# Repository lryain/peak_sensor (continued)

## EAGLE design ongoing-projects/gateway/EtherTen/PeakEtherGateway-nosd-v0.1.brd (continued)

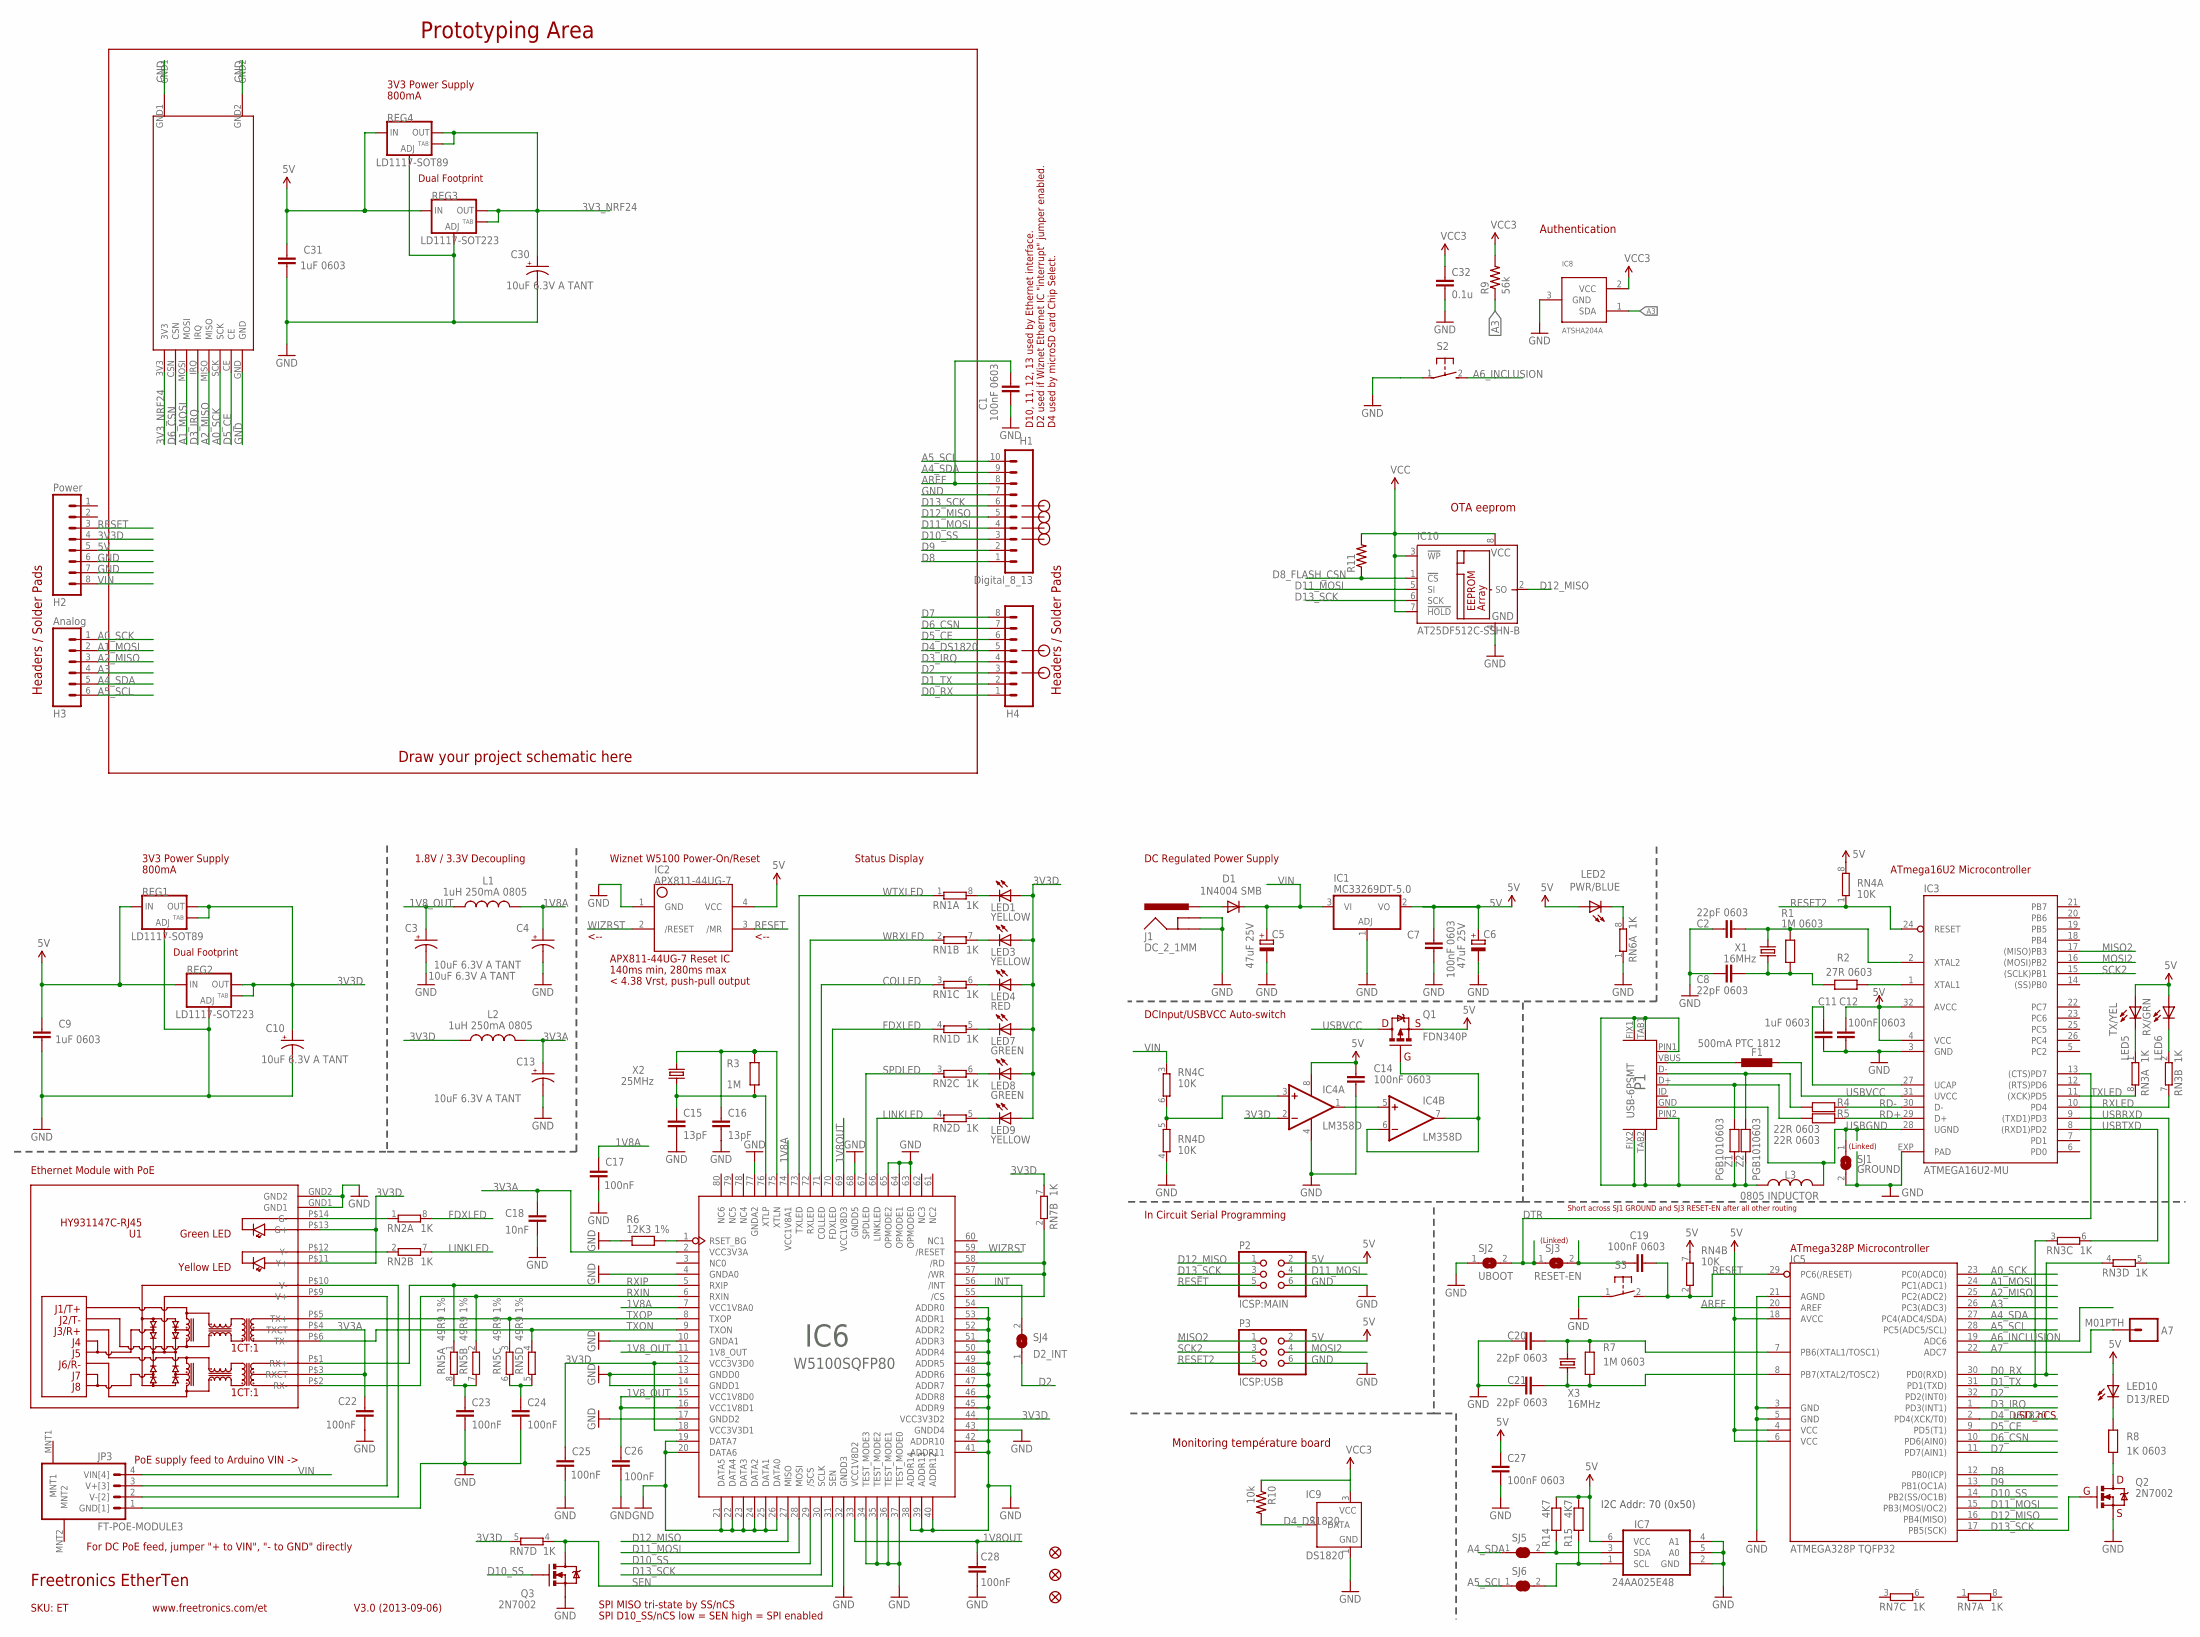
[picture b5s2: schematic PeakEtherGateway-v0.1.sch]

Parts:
A7: M01PTH; 1X01
C1, C7, C12, C14, C19, C27: 100nF 0603; 0603
C2, C8, C20, C21: 22pF 0603; 0603
C3, C4, C10, C13, C30: 10uF 6.3V A TANT; EIA3216
C5, C6: 47uF 25V; PANASONIC_D
C9, C11, C31: 1uF 0603; 0603
C15, C16: 13pF; 0603
C17, C22, C23, C24, C25, C26, C28: 100nF; 0603
C18: 10nF; 0603
C32: 0.1u; 0603-CAP
D1: 1N4004 SMB; SMB-DIODE
F1: 500mA PTC 1812; L1812
FID1, FID2, FID3: FIDUCIAL1X2.5; FIDUCIAL-1X2.5
H1: Digital_8_13; 1X10
H2: Power; 1X08
H3: Analog; 1X06
H4: Digital_0_7; 1X08
IC1: MC33269DT-5.0; DPACK
IC2: APX811-44UG-7; SOT143-R
IC3: ATMEGA16U2-MU; ATMEL_QFN32
IC4: LM358D; SO08
IC5: ATMEGA328P TQFP32; TQFP32-08
IC6: W5100SQFP80; SQFP80
IC7: 24AA025E48; SOT23-6
IC8: ATSHA204A; SOT23
IC9: DS1820; TO92-
IC10: AT25DF512C-SSHN-B; SO-08
J1: DC_2_1MM; POWER_JACK_PTH
JP3: FT-POE-MODULE3; FT-POE-MODULE-NOLABEL
L1, L2: 1uH 250mA 0805; L2012C
L3: 0805 INDUCTOR; 0805-LARGE
LED1, LED3, LED9: YELLOW; LED-0603
LED2: PWR/BLUE; LED-0603
LED4: RED; LED-0603
LED5: TX/YEL; LED-0603
LED6: RX/GRN; LED-0603
LED7, LED8: GREEN; LED-0603
LED10: D13/RED; LED-0603
P1: USB-6PSMT; USB-MICROB-MB05PMXX
P2: ICSP:MAIN; 2X03
P3: ICSP:USB; 2X03
Q1: FDN340P; SOT23
Q2, Q3: 2N7002; SOT23-3
R1, R7: 1M 0603; 0603
R2: 27R 0603; 0603
R3: 1M; 0603
R4, R5: 22R 0603; 0603
R6: 12K3 1%; 0603
R8: 1K 0603; 0603
R9: 56k; 0603-RES
R10: 10k; 0603-RES
R11: RESISTOR0603-RES; 0603-RES
R14, R15: 4K7; 0603
REG1, REG4: LD1117-SOT89; SOT89
REG2, REG3: LD1117-SOT223; SOT223
RN1, RN2, RN3, RN6, RN7: 1K; CAY16
RN4: 10K; CAY16
RN5: 49R9 1%; CAY16
S2, S3: 31-XX; B3F-31XX
SJ1: GROUND; SJ
SJ2: UBOOT; SJ
SJ3: RESET-EN; SJ
SJ4: D2_INT; SJ
SJ5, SJ6: SJCN; SJC
U1: HY931147C-RJ45; HY931147C
U$17: NRF2401; NRF2401_PA_OUTLINE
X1, X3: 16MHz; HC49U-V
X2: 25MHz; HC49U-V
Z1, Z2: PGB1010603; 0603

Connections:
1V8A: C4.A (+), C17.1, IC6.7 (VCC1V8A0), IC6.74 (VCC1V8A1), L1.2
1V8OUT: C28.1, IC6.33 (VCC1V8D2), IC6.69 (VCC1V8D3)
1V8_OUT: C3.A (+), C26.1, IC6.11 (1V8_OUT), IC6.15 (VCC1V8D0), IC6.16 (VCC1V8D1), L1.1
3V3A: C13.A (+), C18.1, C22.1, IC6.2 (VCC3V3A), L2.2, U1.P$3 (RXCT), U1.P$4 (TXCT)
3V3D: C10.A (+), C25.1, H2.4, IC4.2 (-IN), IC6.12 (VCC3V3D0), IC6.18 (VCC3V3D1), IC6.44 (VCC3V3D2), L2.1, LED1.A, LED3.A, LED4.A, LED7.A, LED8.A, LED9.A, REG1.2 (OUT), REG1.4 (OUT), REG2.2 (OUT), REG2.4 (OUT), RN7.5 (2), RN7.7 (2), U1.P$11 (Y+), U1.P$13 (G+)
3V3_NRF24: C30.A (+), C32.1, IC8.2 (VCC), IC9.3 (VCC), IC10.3 (!WP), IC10.7 (!HOLD), IC10.8 (VCC), R9.2, R10.1, R11.2, REG3.2 (OUT), REG3.4 (OUT), REG4.2 (OUT), REG4.4 (OUT), U$17.3V3
5V: C6.+, C7.1, C9.1, C12.1, C14.1, C27.1, C31.1, H2.5, IC1.2 (VO), IC2.4 (VCC), IC3.4 (VCC), IC3.32 (AVCC), IC4.8 (V+), IC5.4 (VCC), IC5.6 (VCC), IC5.18 (AVCC), IC7.6 (VCC), LED2.A, LED5.A, LED6.A, LED10.A, P2.2, P3.2, Q1.2 (S), R14.1, R15.1, REG1.3 (IN), REG2.3 (IN), REG3.3 (IN), REG4.3 (IN), RN4.7 (2), RN4.8 (2)
A0_SCK: H3.1, IC5.23 (PC0(ADC0)), U$17.SCK
A1_MOSI: H3.2, IC5.24 (PC1(ADC1)), U$17.MOSI
A2_MISO: H3.3, IC5.25 (PC2(ADC2)), U$17.MISO
A3: H3.4, IC5.26 (PC3(ADC3)), IC8.1 (SDA), R9.1
A4_SDA: H1.9, H3.5, IC5.27 (PC4(ADC4/SDA)), SJ5.1
A5_SCL: H1.10, H3.6, IC5.28 (PC5(ADC5/SCL)), SJ6.1
A6_INCLUSION: IC5.19 (ADC6), S2.2 (S)
A7: A7.1, IC5.22 (ADC7)
AREF: C1.1, H1.8, IC5.20 (AREF)
COLLED: IC6.71 (COLLED), RN1.3 (1)
D0_RX: H4.1, IC5.30 (PD0(RXD)), RN3.4 (1)
D1_TX: H4.2, IC5.31 (PD1(TXD)), RN3.3 (1)
D2: H4.3, IC5.32 (PD2(INT0)), SJ4.1
D3_IRQ: H4.4, IC5.1 (PD3(INT1)), U$17.IRQ
D4_DS1820: H4.5, IC5.2 (PD4(XCK/T0)), IC9.2 (DATA), R10.2
D5_CE: H4.6, IC5.9 (PD5(T1)), U$17.CE
D6_CSN: H4.7, IC5.10 (PD6(AIN0)), U$17.CSN
D7: H4.8, IC5.11 (PD7(AIN1))
D8: H1.1, IC5.12 (PB0(ICP))
D8_FLASH_CSN: IC10.1 (!CS), R11.1
D9: H1.2, IC5.13 (PB1(OC1A))
D10_SS: H1.3, IC5.14 (PB2(SS/OC1B)), IC6.29 (/SCS), Q3.1 (G)
D11_MOSI: H1.4, IC5.15 (PB3(MOSI/OC2)), IC6.28 (MOSI), IC10.5 (SI), P2.4
D12_MISO: H1.5, IC5.16 (PB4(MISO)), IC6.27 (MISO), IC10.2 (SO), P2.1
D13_SCK: H1.6, IC5.17 (PB5(SCK)), IC6.30 (SCLK), IC10.6 (SCK), P2.3, Q2.1 (G)
DTR: IC3.13 ((CTS)PD7), SJ2.2, SJ3.1
FDXLED: IC6.70 (FDXLED), RN1.4 (1), RN2.8 (2)
GND: C1.2, C2.1, C3.C (-), C4.C (-), C5.-, C6.-, C7.2, C8.1, C9.2, C10.C (-), C11.2, C12.2, C13.C (-), C14.2, C15.2, C16.2, C17.2, C18.2, C20.1, C21.1, C22.2, C23.2, C24.2, C25.2, C26.2, C27.2, C28.2, C30.C (-), C31.2, C32.2, H1.7, H2.6, H2.7, IC1.1 (ADJ), IC2.1 (GND), IC3.3 (GND), IC3.EXP (PAD), IC4.4 (V-), IC5.3 (GND), IC5.5 (GND), IC5.21 (AGND), IC6.4 (GNDA0), IC6.10 (GNDA1), IC6.13 (GNDD0), IC6.14 (GNDD1), IC6.17 (GNDD2), IC6.19 (DATA7), IC6.20 (DATA6), IC6.21 (DATA5), IC6.22 (DATA4), IC6.23 (DATA3), IC6.24 (DATA2), IC6.25 (DATA1), IC6.26 (DATA0), IC6.32 (GNDD3), IC6.34 (TEST_MODE3), IC6.35 (TEST_MODE2), IC6.36 (TEST_MODE1), IC6.37 (TEST_MODE0), IC6.38 (ADDR14), IC6.39 (ADDR13), IC6.40 (ADDR12), IC6.41 (ADDR11), IC6.42 (ADDR10), IC6.43 (GNDD4), IC6.45 (ADDR9), IC6.46 (ADDR8), IC6.47 (ADDR7), IC6.48 (ADDR6), IC6.49 (ADDR5), IC6.50 (ADDR4), IC6.51 (ADDR3), IC6.52 (ADDR2), IC6.53 (ADDR1), IC6.54 (ADDR0), IC6.63 (OPMODE0), IC6.64 (OPMODE1), IC6.65 (OPMODE2), IC6.68 (GNDD5), IC6.77 (GNDA2), IC7.2 (GND), IC7.4 (A1), IC7.5 (A0), IC8.3 (GND), IC9.1 (GND), IC10.4 (GND), J1.GND, J1.GNDBREAK, JP3.1 (GND[1]), P2.6, P3.6, Q2.2 (S), Q3.2 (S), R6.1, REG1.1 (ADJ), REG2.1 (ADJ), REG3.1 (ADJ), REG4.1 (ADJ), RN4.4 (1), RN6.1, S2.1, S3.1, SJ1.2, SJ2.1, U1.GND1, U1.GND2, U$17.GND
INT: IC6.56 (/INT), SJ4.2
LINKLED: IC6.66 (LINKLED), RN2.4 (1), RN2.7 (2)
MISO2: IC3.17 ((MISO)PB3), P3.1
MOSI2: IC3.16 ((MOSI)PB2), P3.4
unnamed: C24.1, RN5.5 (2), RN5.6 (2)
unnamed: C20.2, IC5.7 (PB6(XTAL1/TOSC1)), R7.2, X3.2
unnamed: C19.1, SJ3.2
unnamed: LED10.C, R8.2
unnamed: IC7.1 (SCL), R15.2, SJ6.2
unnamed: Q2.3 (D), R8.1
unnamed: C21.2, IC5.8 (PB7(XTAL2/TOSC2)), R7.1, X3.1
unnamed: IC3.1 (XTAL1), R2.1
unnamed: L3.1, P1.FIX1, P1.FIX2, P1.PIN1, P1.PIN2, P1.TAB1, P1.TAB2, Z1.2, Z2.2
unnamed: LED6.C, RN3.2 (1)
unnamed: IC4.3 (+IN), RN4.5 (2), RN4.6 (2)
unnamed: LED5.C, RN3.1
unnamed: LED2.C, RN6.8 (2)
unnamed: P1.D+, R5.2, Z1.1
unnamed: P1.D-, R4.2, Z2.1
unnamed: IC4.6 (-IN), IC4.7 (OUT), Q1.1 (G)
unnamed: IC4.1 (OUT), IC4.5 (+IN)
unnamed: LED8.C, RN2.6 (2)
unnamed: IC6.55 (/CS), IC6.57 (/WR), IC6.58 (/RD), RN7.2 (1)
unnamed: LED9.C, RN2.5 (2)
unnamed: IC7.3 (SDA), R14.2, SJ5.2
unnamed: D1.A, J1.PWR
unnamed: RN2.1, U1.P$14 (G-)
unnamed: JP3.3 (V+[3]), U1.P$9 (V+)
unnamed: JP3.2 (V-[2]), U1.P$10 (V-)
unnamed: C2.2, IC3.2 (XTAL2), R1.2, X1.2
unnamed: C8.2, R1.1, R2.2, X1.1
unnamed: F1.1, P1.VBUS
unnamed: C11.1, IC3.27 (UCAP)
unnamed: C23.1, RN5.7 (2), RN5.8 (2)
unnamed: IC6.1 (RSET_BG), R6.2
unnamed: LED7.C, RN1.5 (2)
unnamed: LED4.C, RN1.6 (2)
unnamed: LED3.C, RN1.7 (2)
unnamed: LED1.C, RN1.8 (2)
unnamed: RN2.2 (1), U1.P$12 (Y-)
RD+: IC3.29 (D+), R5.1
RD-: IC3.30 (D-), R4.1
RESET: C19.2, H2.3, IC2.3 (/MR), IC5.29 (PC6(/RESET)), P2.5, RN4.2 (1), S3.2 (S)
RESET2: IC3.24 (RESET), P3.5, RN4.1
RXIN: IC6.6 (RXIN), RN5.2 (1), U1.P$2 (RX-)
RXIP: IC6.5 (RXIP), RN5.1, U1.P$1 (RX+)
RXLED: IC3.10 (PD4), RN3.7 (2)
SCK2: IC3.15 ((SCLK)PB1), P3.3
SEN: IC6.31 (SEN), Q3.3 (D), RN7.4 (1)
SPDLED: IC6.67 (SPDLED), RN2.3 (1)
TXLED: IC3.11 ((XCK)PD5), RN3.8 (2)
TXON: IC6.9 (TXON), RN5.4 (1), U1.P$6 (TX-)
TXOP: IC6.8 (TXOP), RN5.3 (1), U1.P$5 (TX+)
USBGND: IC3.28 (UGND), L3.2, P1.GND, SJ1.1
USBRXD: IC3.9 ((TXD1)PD3), RN3.5 (2)
USBTXD: IC3.8 ((RXD1)PD2), RN3.6 (2)
USBVCC: F1.2, IC3.31 (UVCC), Q1.3 (D)
VIN: C5.+, D1.C, H2.8, IC1.3 (VI), JP3.4 (VIN[4]), RN4.3 (1)
WIZRST: IC2.2 (/RESET), IC6.59 (/RESET)
WRXLED: IC6.72 (RXLED), RN1.2 (1)
WTXLED: IC6.73 (TXLED), RN1.1
XTLN: C16.1, IC6.75 (XTLN), R3.2, X2.2
XTLP: C15.1, IC6.76 (XTLP), R3.1, X2.1

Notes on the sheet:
Prototyping Area
SKU: ET
3V3 Power Supply
Status Display
Headers / Solder Pads
Dual Footprint
1.8V / 3.3V Decoupling
Draw your project schematic here
D10, 11, 12, 13 used by Ethernet interface.
D2 used if Wiznet Ethernet IC "interrupt" jumper enabled.
PoE supply feed to Arduino VIN ->
SPI MISO tri-state by SS/nCS
SPI D10_SS/nCS low = SEN high = SPI enabled
For DC PoE feed, jumper "+ to VIN", "- to GND" directly
DC Regulated Power Supply
ATmega328P Microcontroller
APX811-44UG-7 Reset IC
140ms min, 280ms max
ATmega16U2 Microcontroller
DCInput/USBVCC Auto-switch
Wiznet W5100 Power-On/Reset
uSD_nCS
800mA
In Circuit Serial Programming
Freetronics EtherTen
V3.0 (2013-09-06)
www.freetronics.com/et
Ethernet Module with PoE
< 4.38 Vrst, push-pull output
<--
D4 used by microSD card Chip Select.
(Linked)
Short across SJ1 GROUND and SJ3 RESET-EN after all other routing
I2C Addr: 70 (0x50)
Authentication
Monitoring température board
OTA eeprom

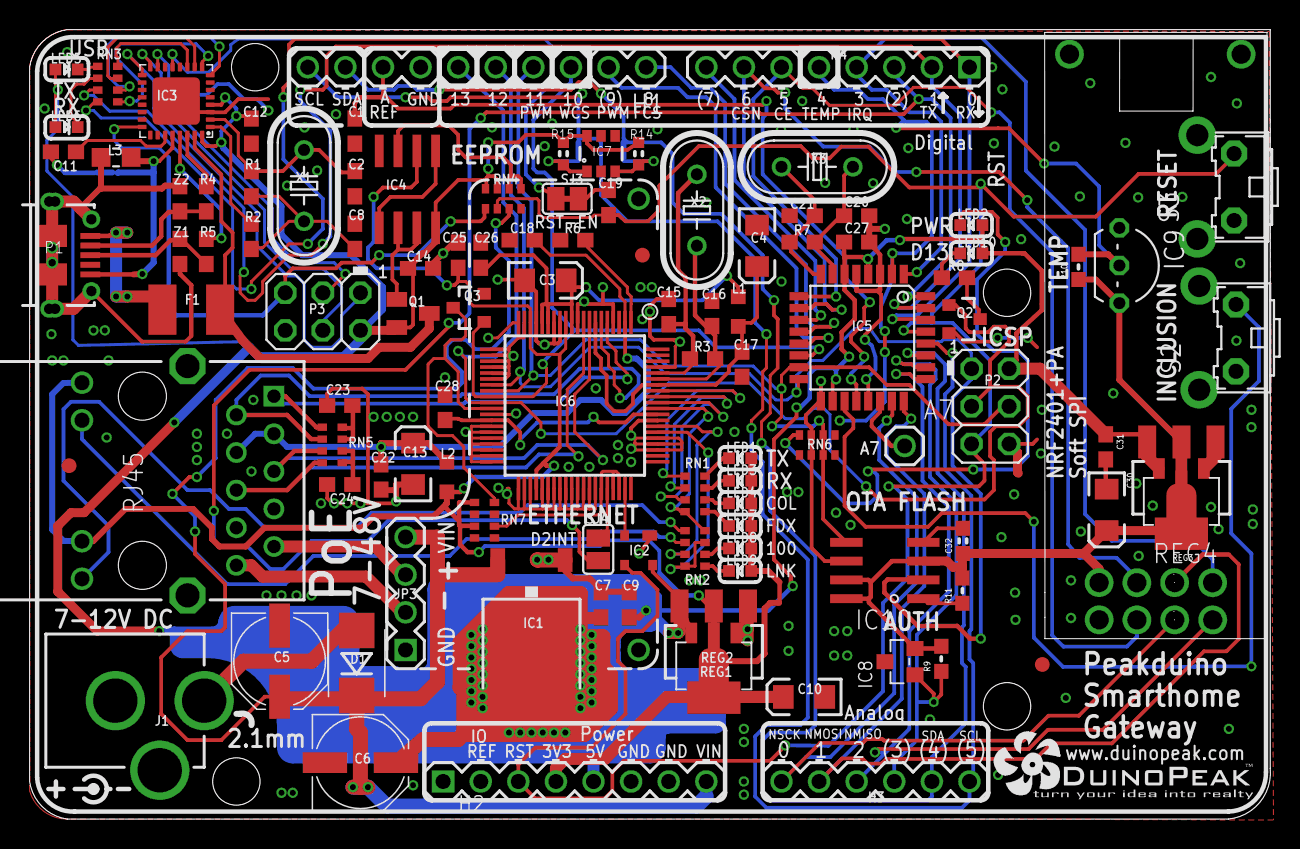
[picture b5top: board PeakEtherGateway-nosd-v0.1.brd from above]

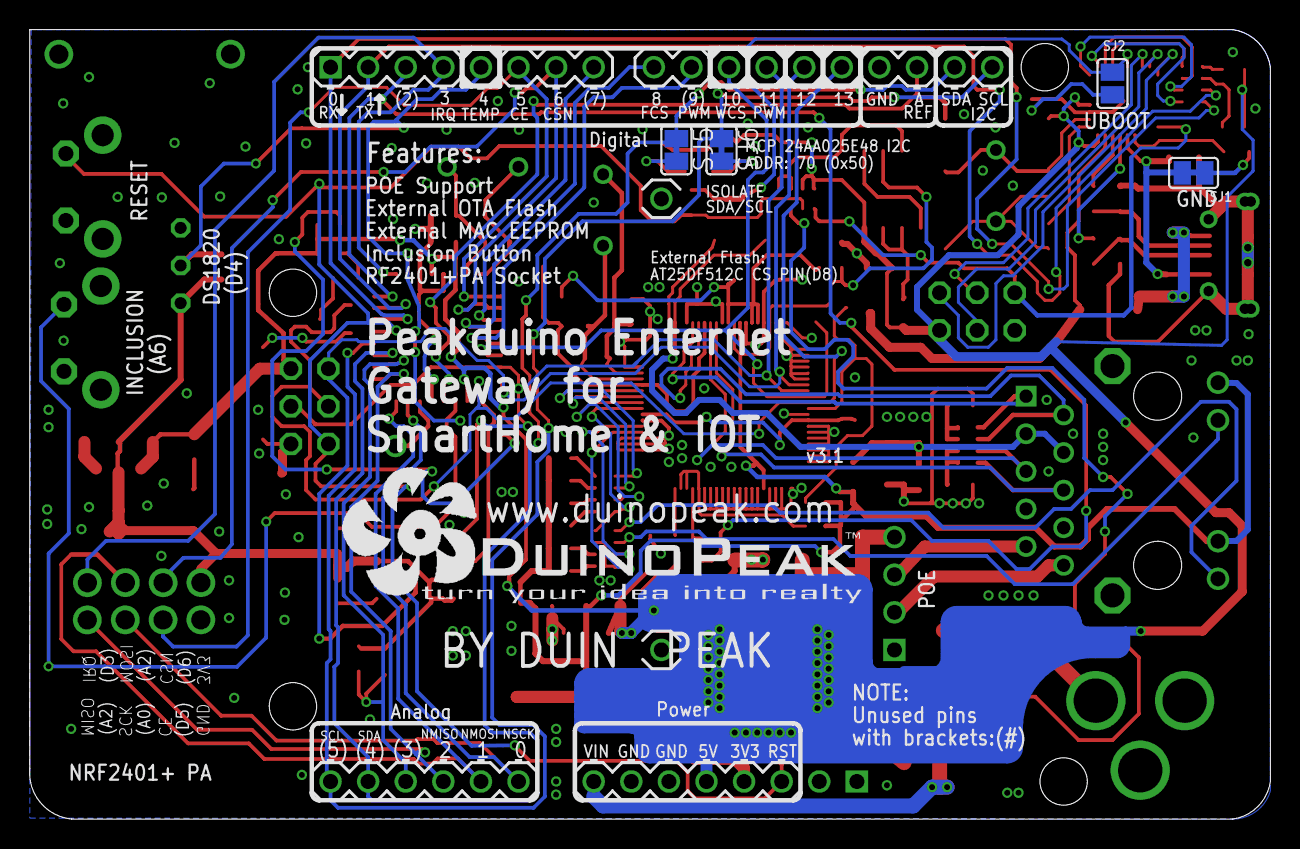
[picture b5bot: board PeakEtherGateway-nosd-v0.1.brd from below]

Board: 2 copper layers, 83.8 x 53.3 mm, 113 parts (5 on the bottom side), 98 nets.

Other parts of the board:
U$8: DUINOPEAK-LOGO-1.2
U$20: DUINOPEAK-LOGO-0.6

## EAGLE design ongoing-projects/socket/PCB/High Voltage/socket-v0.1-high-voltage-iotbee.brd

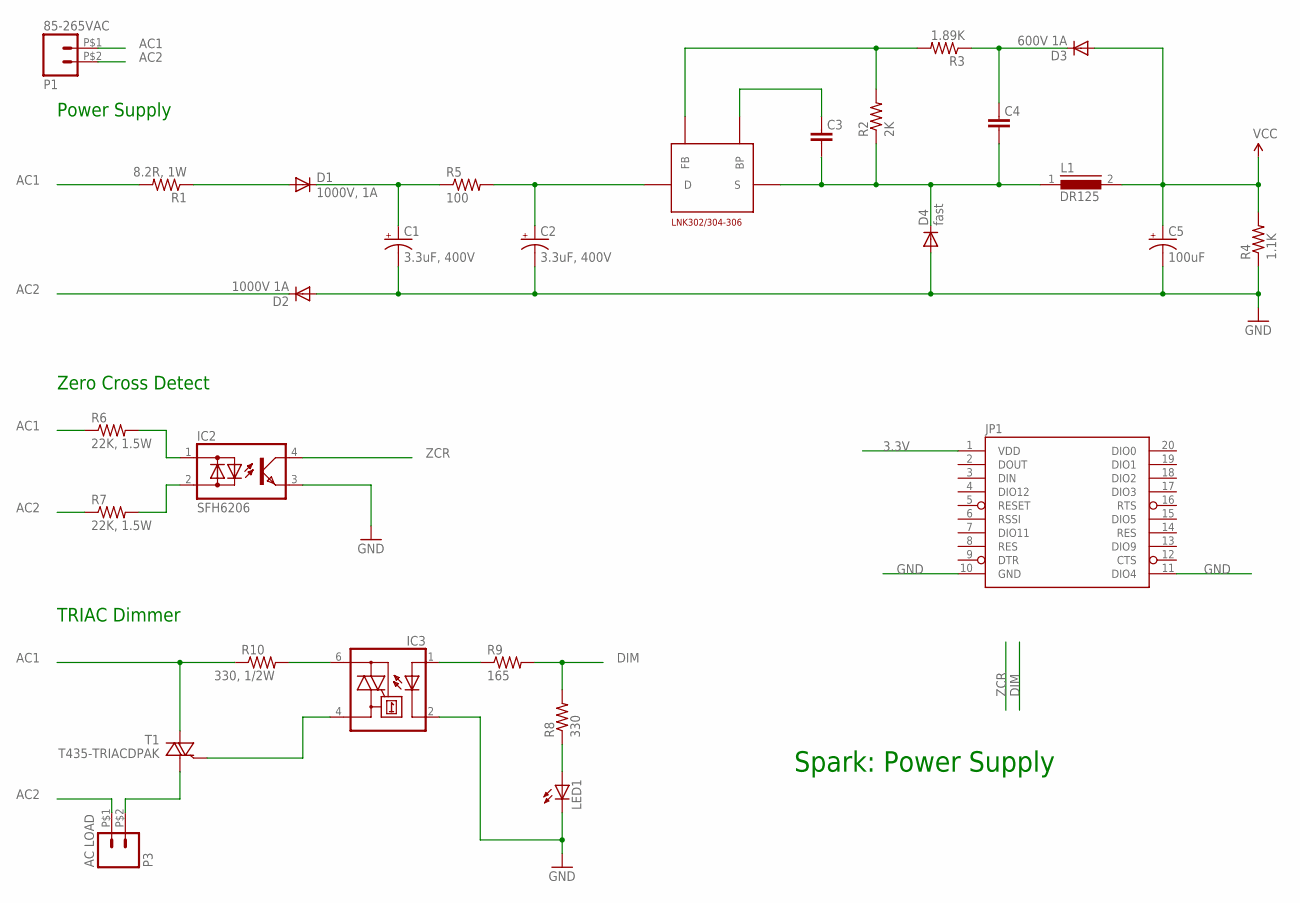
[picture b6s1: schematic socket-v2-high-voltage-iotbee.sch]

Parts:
C1, C2: 3.3uF, 400V; E3,5-8
C3: 0.1uF; 0603-CAP
C4: 10uF, 50V; 0805
C5: 100uF; EIA3528
D1: 1000V, 1A; SMA-DIODE
D2: 1000V 1A; SMA-DIODE
D3: 600V 1A; SMA-DIODE
D4: fast; SMA-DIODE
IC1: LNK302/304-306; SMD-8B
IC2: SFH6206; DIL4-SMD
IC3: MOC3031S; DIL6-SMD; MPN MOC3031SM
JP1: XBEE-1B3; XBEE-SMD
L1: DR125
LED1: LED0603; LED-0603
P1: 85-265VAC; 1X02_BIG
P3: AC LOAD; 1X02_BIG
R1: 8.2R, 1W; 0207/10
R2: 2K; 0805
R3: 1.89K; 0805
R4: 1.1K; 0603-RES
R5: 100; 0204/7
R6, R7: 22K, 1.5W; R2512
R8: 330; 0805
R9: 165; 0805
R10: 330, 1/2W; R1210
T1: T435-TRIACDPAK; TO252

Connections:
3.3V: C5.A (+), D3.A, JP1.1, JP1.10, L1.2, R4.2; also elsewhere on the board
$N$100: C3.1, C4.1, D4.C, IC1.S1 (S), L1.1, R2.1
$N$101: C2.+, IC1.D, R5.2
AC1: P1.P$1 (1), R1.2, R6.1, R10.1, T1.2 (A2)
AC2: D2.C, P1.P$2 (2), P3.P$1 (1), R7.1
DIM: R8.2, R9.2; also elsewhere on the board
GND: C1.-, C2.-, C5.C (-), D2.A, D4.A, IC2.3 (E), IC3.2 (C), JP1.1, JP1.10, JP1.11 (DIO4), LED1.C, R4.1; also elsewhere on the board
unnamed: C4.2, D3.C, R3.1
unnamed: C3.2, IC1.BP
unnamed: IC3.1 (A), R9.1
unnamed: IC3.6 (A2), R10.2
unnamed: IC3.4 (A1), T1.3 (G)
unnamed: P3.P$2 (2), T1.1 (A1)
unnamed: IC2.1 (AC1), R6.2
unnamed: LED1.A, R8.1
unnamed: C1.+, D1.C, R5.1
unnamed: IC1.FB, R2.2, R3.2
unnamed: IC2.2 (AC2), R7.2
RAW_PR: D1.A, R1.1
ZCR: IC2.4 (C); also elsewhere on the board

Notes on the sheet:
Power Supply
Spark: Power Supply
Zero Cross Detect
TRIAC Dimmer

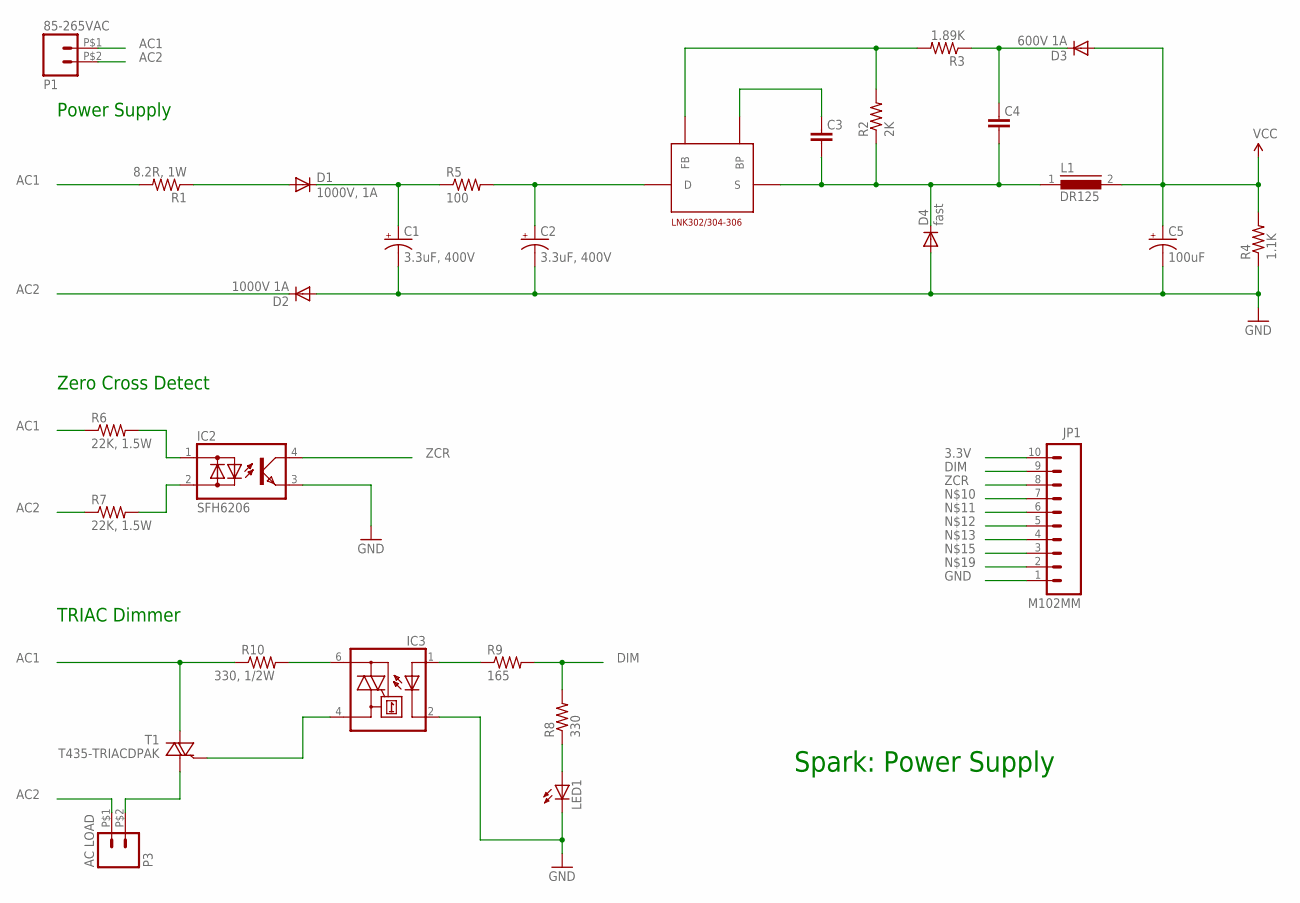
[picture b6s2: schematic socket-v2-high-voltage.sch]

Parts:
C1, C2: 3.3uF, 400V; E3,5-8
C3: 0.1uF; 0603-CAP
C4: 10uF, 50V; 0805
C5: 100uF; EIA3528
D1: 1000V, 1A; SMA-DIODE
D2: 1000V 1A; SMA-DIODE
D3: 600V 1A; SMA-DIODE
D4: fast; SMA-DIODE
IC1: LNK302/304-306; SMD-8B
IC2: SFH6206; DIL4-SMD
IC3: MOC3031S; DIL6-SMD; MPN MOC3031SM
JP1: M102MM; 1X10-2MM
L1: DR125
LED1: LED0603; LED-0603
P1: 85-265VAC; 1X02_BIG
P3: AC LOAD; 1X02_BIG
R1: 8.2R, 1W; 0207/10
R2: 2K; 0805
R3: 1.89K; 0805
R4: 1.1K; 0603-RES
R5: 100; 0204/7
R6, R7: 22K, 1.5W; R2512
R8: 330; 0805
R9: 165; 0805
R10: 330, 1/2W; R1210
T1: T435-TRIACDPAK; TO252

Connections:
3.3V: C5.A (+), D3.A, JP1.1, JP1.10, L1.2, R4.2; also elsewhere on the board
$N$100: C3.1, C4.1, D4.C, IC1.S1 (S), L1.1, R2.1
$N$101: C2.+, IC1.D, R5.2
AC1: P1.P$1 (1), R1.2, R6.1, R10.1, T1.2 (A2)
AC2: D2.C, P1.P$2 (2), P3.P$1 (1), R7.1
DIM: JP1.9, R8.2, R9.2; also elsewhere on the board
GND: C1.-, C2.-, C5.C (-), D2.A, D4.A, IC2.3 (E), IC3.2 (C), JP1.1, JP1.10, LED1.C, R4.1; also elsewhere on the board
unnamed: C4.2, D3.C, R3.1
unnamed: C3.2, IC1.BP
unnamed: IC3.1 (A), R9.1
unnamed: IC3.6 (A2), R10.2
unnamed: IC3.4 (A1), T1.3 (G)
unnamed: P3.P$2 (2), T1.1 (A1)
unnamed: IC2.1 (AC1), R6.2
unnamed: LED1.A, R8.1
unnamed: C1.+, D1.C, R5.1
unnamed: IC1.FB, R2.2, R3.2
unnamed: IC2.2 (AC2), R7.2
RAW_PR: D1.A, R1.1
ZCR: IC2.4 (C), JP1.8; also elsewhere on the board

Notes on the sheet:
Power Supply
Spark: Power Supply
Zero Cross Detect
TRIAC Dimmer

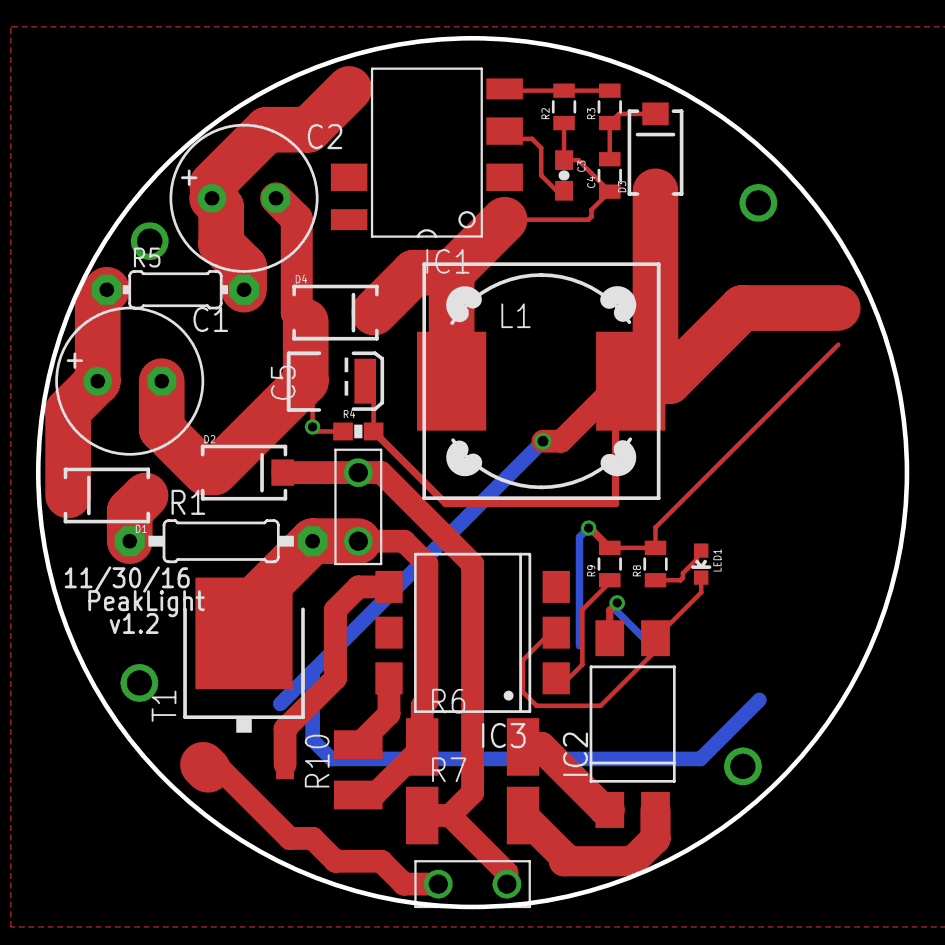
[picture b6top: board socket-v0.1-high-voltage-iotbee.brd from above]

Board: 2 copper layers, 48.3 x 48.3 mm, 28 parts (1 on the bottom side), 20 nets.

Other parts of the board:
U1: IOT_BEE_SMD

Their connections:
3.3V: U1.3V3; also elsewhere on the board
DIM: U1.D3; also elsewhere on the board
GND: U1.A3, U1.GND; also elsewhere on the board
ZCR: U1.D4; also elsewhere on the board
